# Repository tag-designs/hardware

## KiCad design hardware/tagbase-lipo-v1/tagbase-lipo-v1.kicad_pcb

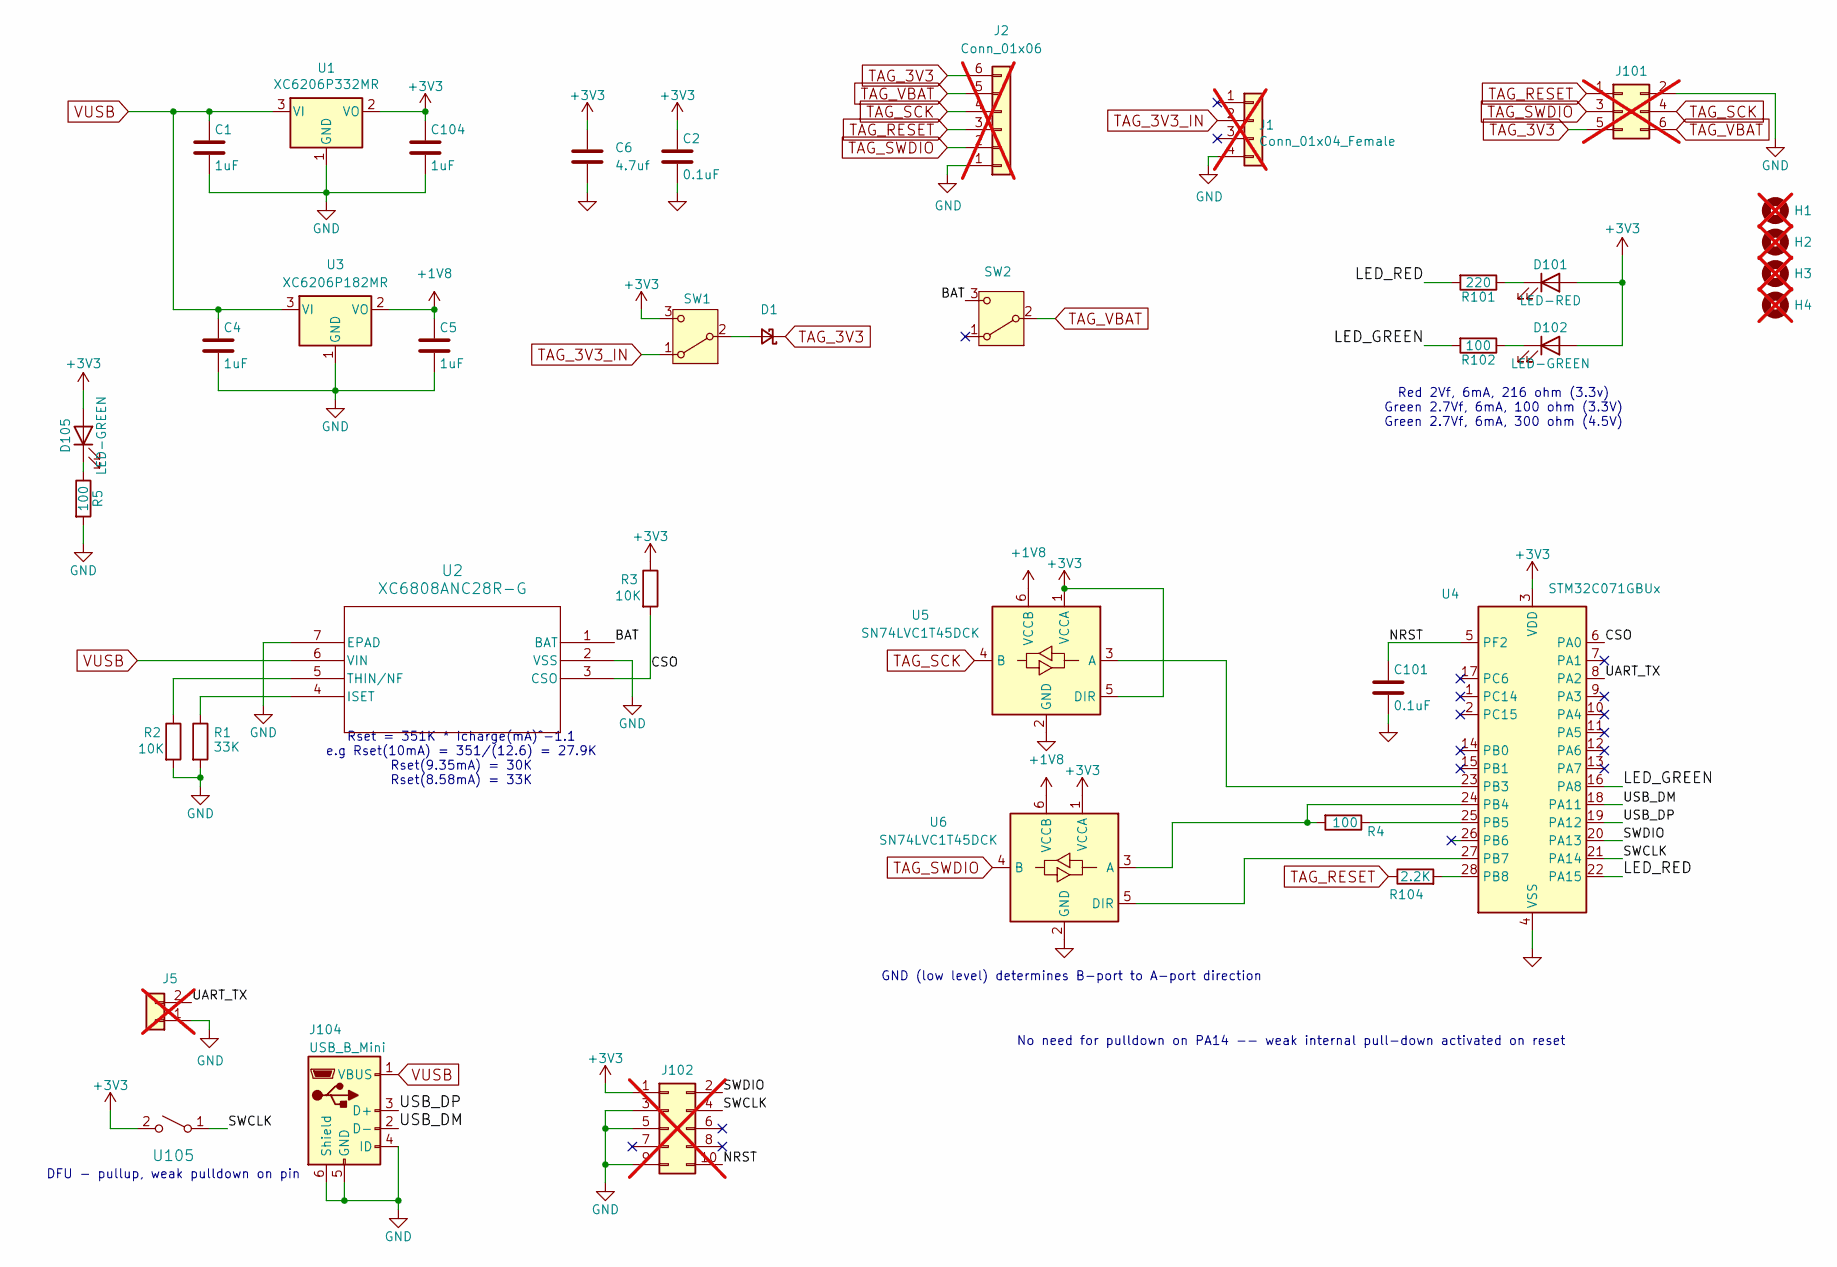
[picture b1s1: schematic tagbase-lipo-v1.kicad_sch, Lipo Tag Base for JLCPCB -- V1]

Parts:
C1, C4, C5, C104: 1uF; C_0402_1005Metric; MPN CL05A105KA5NQNC; LCSC C52923
C2, C101: 0.1uF; C_0402_1005Metric; MPN CL05B104KO5NNNC; LCSC C1525
C6: 4.7uf; C_0402_1005Metric; MPN CL05A475MP5NRNC; LCSC C23733
D1: D_Schottky_Small; D_SOD-323; MPN 1N5819WS; LCSC C191023
D101: LED-RED; D_0805_2012Metric; MPN NCD0805R1; LCSC C84256
D102, D105: LED-GREEN; D_0805_2012Metric; MPN KT-0805G; LCSC C2297
H1, H2, H3, H4: MountingHole; MountingHole_2.5mm; not fitted
J1: Conn_01x04_Female; JST_XH_B04B-XH-AM_1x04_P2.50mm_Vertical; not fitted
J2: Conn_01x06; JST_B6B-ZR(LF)(SN); not fitted
J5: Conn_01x02; PinHeader_1x02_P2.54mm_Vertical; not fitted
J101: Conn_02x03_Odd_Even; 6pin_tagpoints_double_screws; not fitted
J102: Conn_02x05_Odd_Even; FTSH-105-01-F-D-K; not fitted
J104: USB_B_Mini; USB_Mini-B; MPN MINI 5PTP; LCSC C2681563
R1: 33K; R_0402_1005Metric; MPN 0402WGF3302TCE; LCSC C25779
R2, R3: 10K; R_0402_1005Metric; MPN 0402WGF1002TCE; LCSC C25744
R4: 100; R_0402_1005Metric; MPN 0402WGF1000TCE; LCSC C25076
R5, R102: 100; R_0603_1608Metric; MPN 0603WAF1000T5E; LCSC C22775
R101: 220; R_0603_1608Metric; MPN 0603WAF1000T5E; LCSC C22775
R104: 2.2K; R_0402_1005Metric; MPN 0402WGF2201TCE; LCSC C25879
SW1, SW2: SW_SPDT; CJS-1200B_NDC; MPN CJS-1201B; LCSC C132858
U1: XC6206P332MR; SOT-23-3; MPN XC6206P332MR; LCSC C5446
U2: XC6808ANC28R-G; USP-6B_TOR; MPN XC6808A4C28R-G; LCSC C3682502
U3: XC6206P182MR; SOT-23-3; MPN XC6206P182MR-G; LCSC C21659
U4: STM32C071GBUx; QFN-28_4x4mm_P0.5mm
U5, U6: SN74LVC1T45DCK; SOT-363_SC-70-6
U105: Tactile Switch; SW_SPST_TS_1187; MPN TS-1187A-C-E-B; LCSC C318889

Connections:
+1V8: C5.1, U3.2 (VO), U5.6 (VCCB), U6.6 (VCCB)
+3V3: C2.1, C6.1, C104.1, D101.2 (A), D102.2 (A), D105.2 (A), J102.1, R3.1, SW1.3 (C), U1.2 (VO), U4.3 (VDD), U5.1 (VCCA), U5.5 (DIR), U6.1 (VCCA), U105.2 (B)
/BAT: SW2.3 (C), U2.1 (BAT)
/CSO: R3.2, U2.3 (CSO), U4.6 (PA0)
/LED_GREEN: R102.2, U4.16 (PA8)
/LED_RED: R101.2, U4.22 (PA15)
/NRST: C101.1, J102.10, U4.5 (PF2)
/SWCLK: J102.4, U4.21 (PA14), U105.1 (A)
/SWDIO: J102.2, U4.20 (PA13)
/UART_TX: J5.2, U4.8 (PA2)
/USB_DM: J104.2 (D-), U4.18 (PA11)
/USB_DP: J104.3 (D+), U4.19 (PA12)
GND: C1.2, C2.2, C4.2, C5.2, C6.2, C101.2, C104.2, J1.4, J2.1, J5.1, J101.2, J102.3, J102.5, J102.9, J104.4 (ID), J104.5 (GND), J104.6 (Shield), R1.2, R2.2, R5.2, U1.1 (GND), U2.2 (VSS), U2.7 (EPAD), U3.1 (GND), U4.4 (VSS), U5.2 (GND), U6.2 (GND)
unnamed: D1.2 (A), SW1.2 (B)
unnamed: D101.1 (K), R101.1
unnamed: D102.1 (K), R102.1
unnamed: D105.1 (K), R5.1
unnamed: R1.1, U2.4 (ISET)
unnamed: R2.1, U2.5 (THIN/NF)
unnamed: U4.23 (PB3), U5.3 (A)
unnamed: R4.2, U4.24 (PB4), U6.3 (A)
unnamed: R4.1, U4.25 (PB5)
unnamed: U4.27 (PB7), U6.5 (DIR)
unnamed: R104.2, U4.28 (PB8)
TAG_3V3: D1.1 (K), J2.6, J101.5
TAG_3V3_IN: J1.2, SW1.1 (A)
TAG_RESET: J2.3, J101.1, R104.1
TAG_SCK: J2.4, J101.4, U5.4 (B)
TAG_SWDIO: J2.2, J101.3, U6.4 (B)
TAG_VBAT: J2.5, J101.6, SW2.2 (B)
VUSB: C1.1, C4.1, J104.1 (VBUS), U1.3 (VI), U2.6 (VIN), U3.3 (VI)

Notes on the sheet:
Rset = 351K * Icharge(mA)^-1.1 e.g Rset(10mA) = 351/(12.6) = 27.9K Rset(9.35mA) = 30K Rset(8.58mA) = 33K
GND (low level) determines B-port to A-port direction
No need for pulldown on PA14 -- weak internal pull-down activated on reset
DFU - pullup, weak pulldown on pin
Red 2Vf, 6mA, 216 ohm (3.3v) Green 2.7Vf, 6mA, 100 ohm (3.3V) Green 2.7Vf, 6mA, 300 ohm (4.5V)

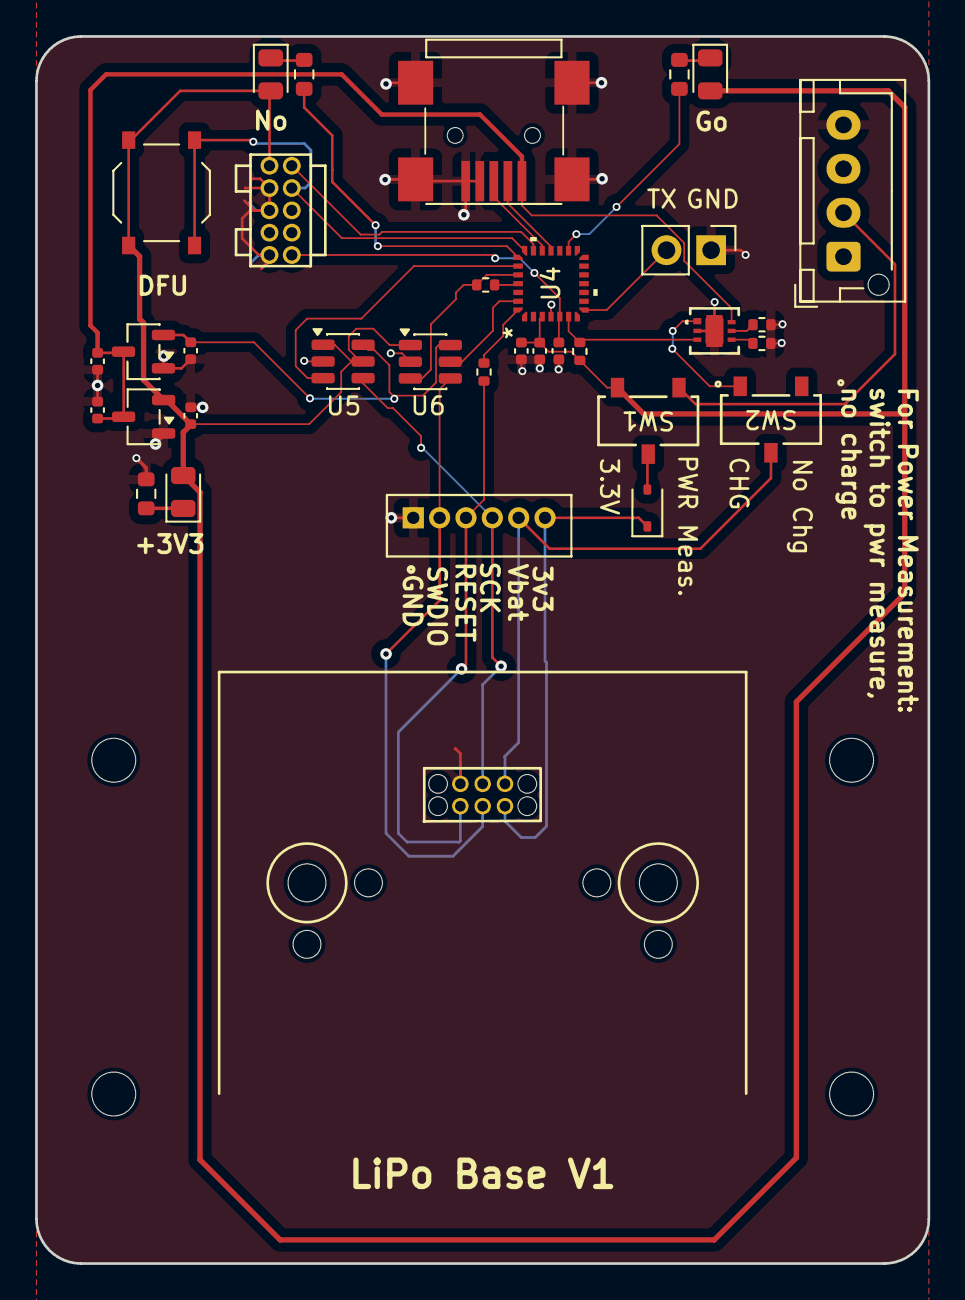
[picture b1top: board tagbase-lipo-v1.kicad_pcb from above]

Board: 2 copper layers, 50.8 x 69.9 mm, 38 parts (0 on the bottom side), 31 nets.

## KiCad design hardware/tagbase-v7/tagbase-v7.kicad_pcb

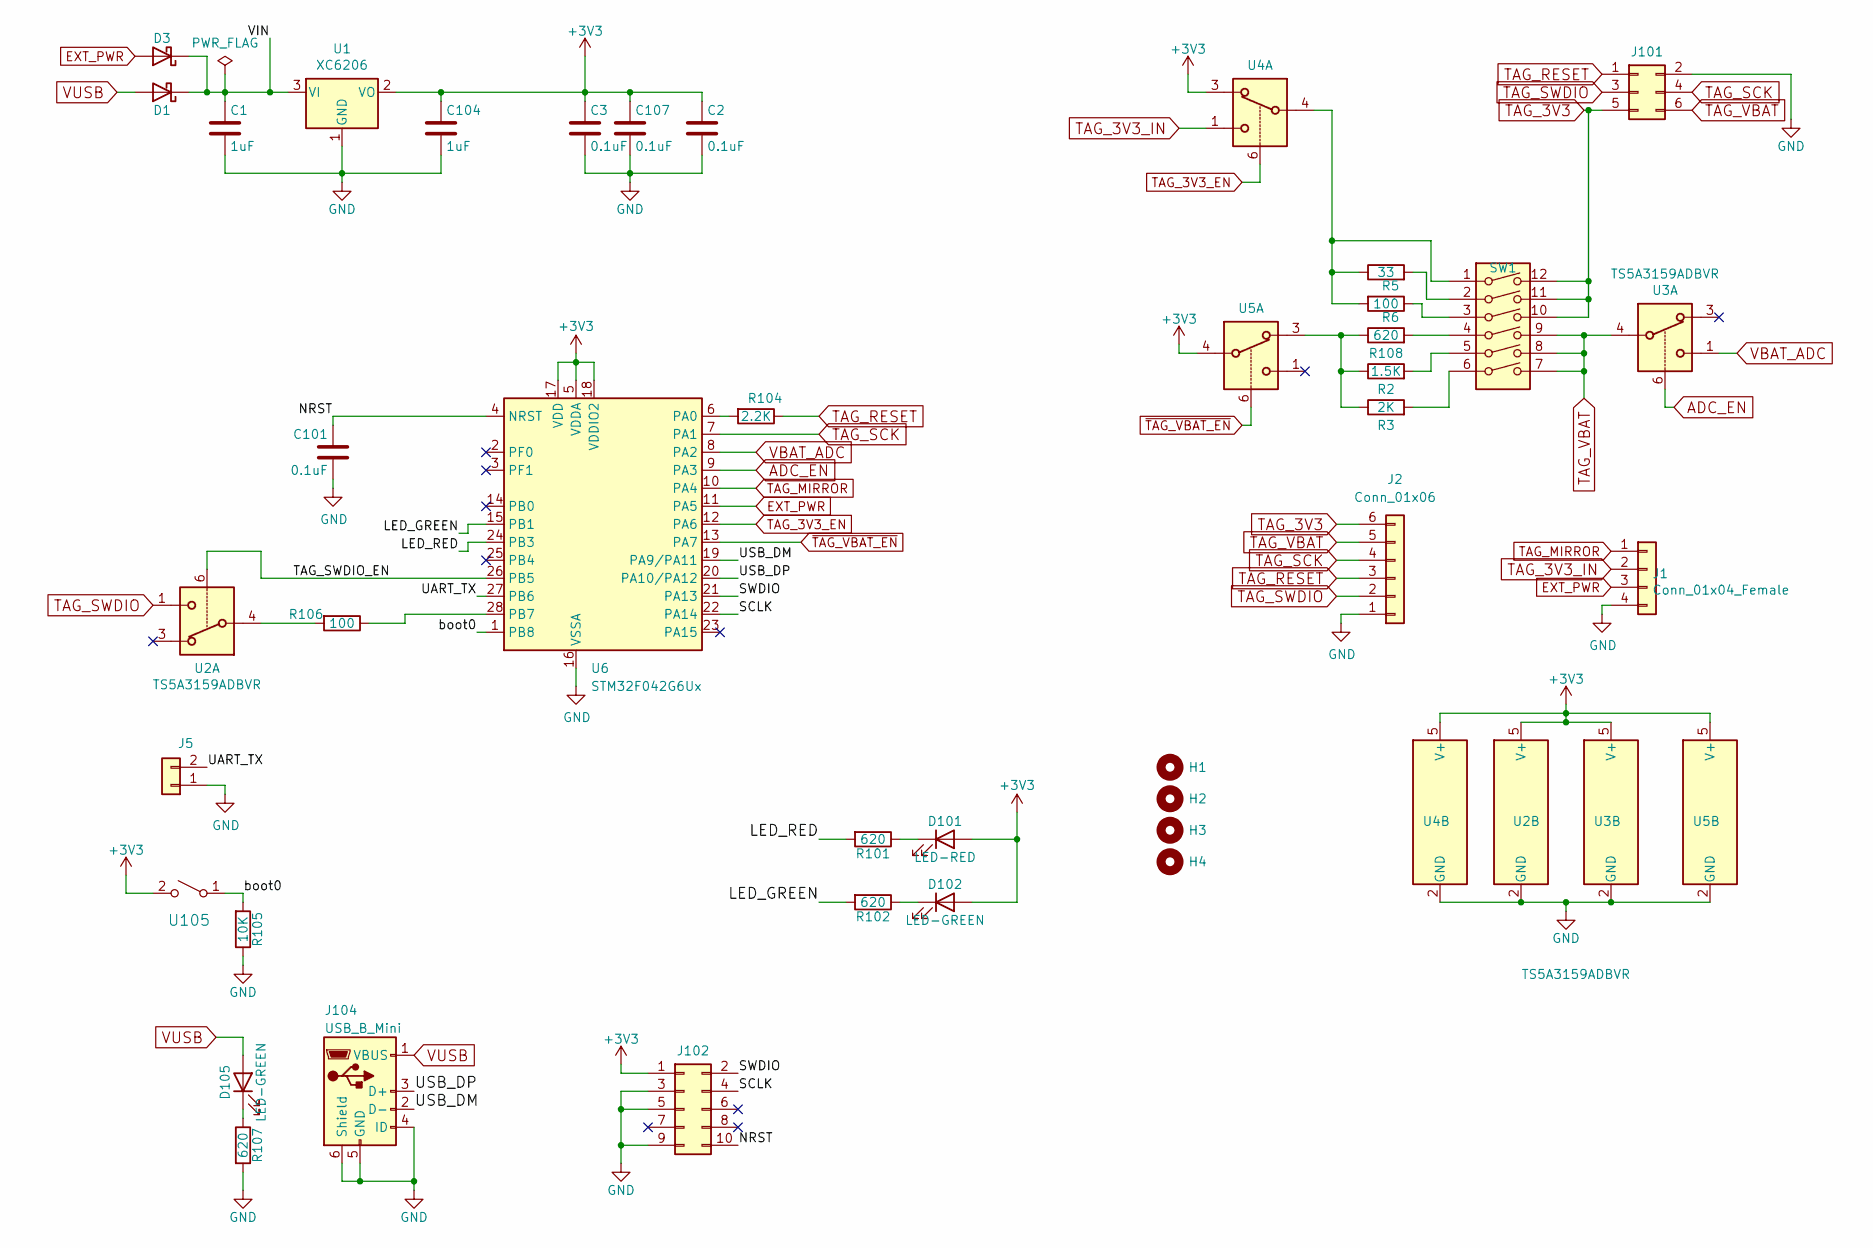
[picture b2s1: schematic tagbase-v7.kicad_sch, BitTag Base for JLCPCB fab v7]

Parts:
C1, C104: 1uF; C_0603_1608Metric; MPN CL10A105KB8NNNC; LCSC C15849
C2, C3, C101, C107: 0.1uF; C_0603_1608Metric; MPN CC0603KRX7R9BB104; LCSC C14663
D1, D3: DIODE; D_SOD-123; MPN B5819W; LCSC C8598
D101: LED-RED; LED_0603_1608Metric; MPN KT-0603R; LCSC C2286
D102, D105: LED-GREEN; LED_0603_1608Metric; MPN 19-217/GHC-YR1S2/3T; LCSC C72043
H1, H2, H3, H4: MountingHole; MountingHole_2.5mm
J1: Conn_01x04_Female; JST_XH_B04B-XH-AM_1x04_P2.50mm_Vertical
J2: Conn_01x06; JST_B6B-ZR(LF)(SN)
J5: Conn_01x02; PinHeader_1x02_P2.54mm_Vertical
J101: Conn_02x03_Odd_Even; 6pin_tagpoints_new_offset
J102: Conn_02x05_Odd_Even; FTSH-105-01-F-D-K
J104: USB_B_Mini; USB_Mini-B; MPN MINI 5PTP; LCSC C2681563
R2: 1.5K; R_0603_1608Metric; MPN 0603WAF1501T5E; LCSC C22843
R3: 2K; R_0603_1608Metric; MPN 0603WAF2001T5E; LCSC C22975
R5: 33; R_0603_1608Metric; MPN 0603WAF330JT5E; LCSC C23140
R6, R106: 100; R_0603_1608Metric; MPN 0603WAF1000T5E; LCSC C22775
R101, R102, R107, R108: 620; R_0603_1608Metric; MPN 0603WAF6200T5E; LCSC C23220
R104: 2.2K; R_0603_1608Metric; MPN 0603WAF1002T5E; LCSC C4190
R105: 10K; R_0603_1608Metric; MPN 0603WAF1002T5E; LCSC C25804
SW1: SW_DIP_x04; SW_DIP_SPSTx06_Slide_KingTek_DSHP06TS_W7.62mm_P1.27mm; MPN DSHP06TSGER; LCSC C3293146
U1: XC6206; SOT-23-3; MPN XC6206P332MR; LCSC C5446
U2, U3, U4, U5: TS5A3159ADBVR; SOT-23-6; MPN TS5A3159ADBVR; LCSC C128405
U6: STM32F042G6Ux; QFN-28_4x4mm_P0.5mm; MPN STM32F042G6U6; LCSC C961597
U105: Tactile Switch; SW_SPST_TS_1187; MPN TS-1187A-C-E-B; LCSC C318889

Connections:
+3V3: C2.1, C3.1, C104.1, C107.1, D101.2 (A), D102.2 (A), J102.1, U1.2 (VO), U2.5 (V+), U3.5 (V+), U4.3, U4.5 (V+), U5.4, U5.5 (V+), U6.5 (VDDA), U6.17 (VDD), U6.18 (VDDIO2), U105.2 (B)
/LED_GREEN: R102.2, U6.15 (PB1)
/LED_RED: R101.2, U6.24 (PB3)
/NRST: C101.1, J102.10, U6.4 (NRST)
/SCLK: J102.4, U6.22 (PA14)
/SWDIO: J102.2, U6.21 (PA13)
/TAG_SWDIO_EN: U2.6, U6.26 (PB5)
/UART_TX: J5.2, U6.27 (PB6)
/USB_DM: J104.2 (D-), U6.19 (PA9/PA11)
/USB_DP: J104.3 (D+), U6.20 (PA10/PA12)
/VIN: C1.1, D1.1 (K), D3.1 (K), U1.3 (VI)
/boot0: R105.2, U6.1 (PB8), U105.1 (A)
ADC_EN: U3.6, U6.9 (PA3)
EXT_PWR: D3.2 (A), J1.3, U6.11 (PA5)
GND: C1.2, C2.2, C3.2, C101.2, C104.2, C107.2, J1.4, J2.1, J5.1, J101.2, J102.3, J102.5, J102.9, J104.4 (ID), J104.5 (GND), J104.6 (Shield), R105.1, R107.2, U1.1 (GND), U2.2 (GND), U3.2 (GND), U4.2 (GND), U5.2 (GND), U6.16 (VSSA)
unnamed: D101.1 (K), R101.1
unnamed: D102.1 (K), R102.1
unnamed: D105.1 (K), R107.1
unnamed: R2.2, SW1.5
unnamed: R3.2, SW1.6
unnamed: R5.1, R6.2, SW1.1, U4.4
unnamed: R5.2, SW1.2
unnamed: R6.1, SW1.3
unnamed: R104.2, U6.6 (PA0)
unnamed: R106.1, U6.28 (PB7)
unnamed: R106.2, U2.4
unnamed: R2.1, R3.1, R108.1, U5.3
unnamed: R108.2, SW1.4
TAG_3V3: J2.6, J101.5, SW1.10, SW1.11, SW1.12
TAG_3V3_EN: U4.6, U6.12 (PA6)
TAG_3V3_IN: J1.2, U4.1
TAG_MIRROR: J1.1, U6.10 (PA4)
TAG_RESET: J2.3, J101.1, R104.1
TAG_SCK: J2.4, J101.4, U6.7 (PA1)
TAG_SWDIO: J2.2, J101.3, U2.1
TAG_VBAT: J2.5, J101.6, SW1.7, SW1.8, SW1.9, U3.4
VBAT_ADC: U3.1, U6.8 (PA2)
VUSB: D1.2 (A), D105.2 (A), J104.1 (VBUS)
~TAG_VBAT_EN: U5.6, U6.13 (PA7)

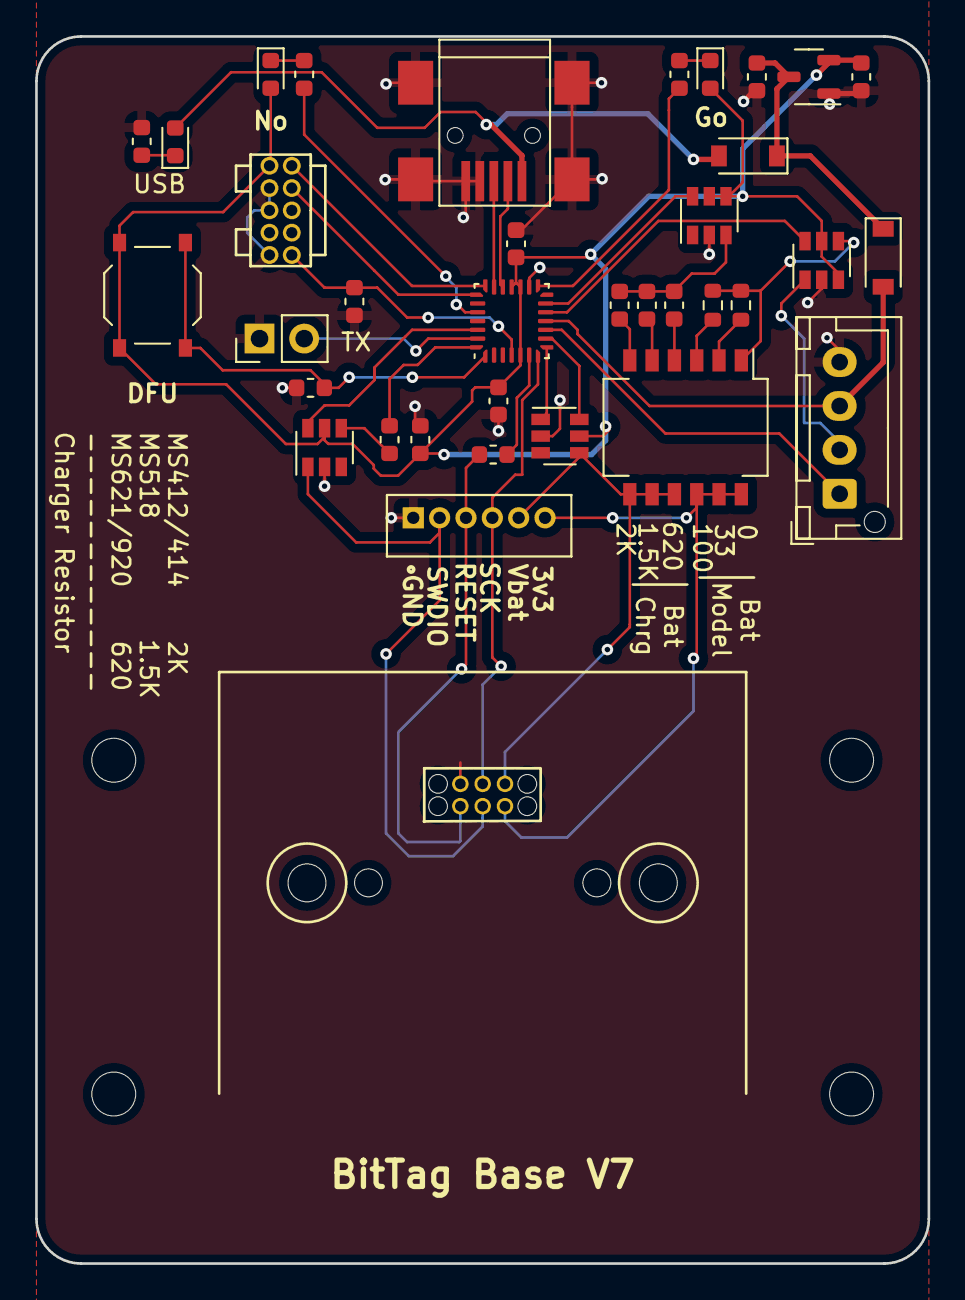
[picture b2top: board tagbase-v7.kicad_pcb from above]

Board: 2 copper layers, 50.8 x 69.9 mm, 40 parts (0 on the bottom side), 39 nets.
